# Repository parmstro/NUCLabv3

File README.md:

# NUCLabv3
Drawings, parts lists and instructions on building the latest version of NUC Lab.
Case Drawings use NewPowerBoardwPositioningHoles.fzz for power distribution board.

This is NUCLab3_Chassis1 (See the [Wiki](https://github.com/parmstro/NUCLabv3/wiki))

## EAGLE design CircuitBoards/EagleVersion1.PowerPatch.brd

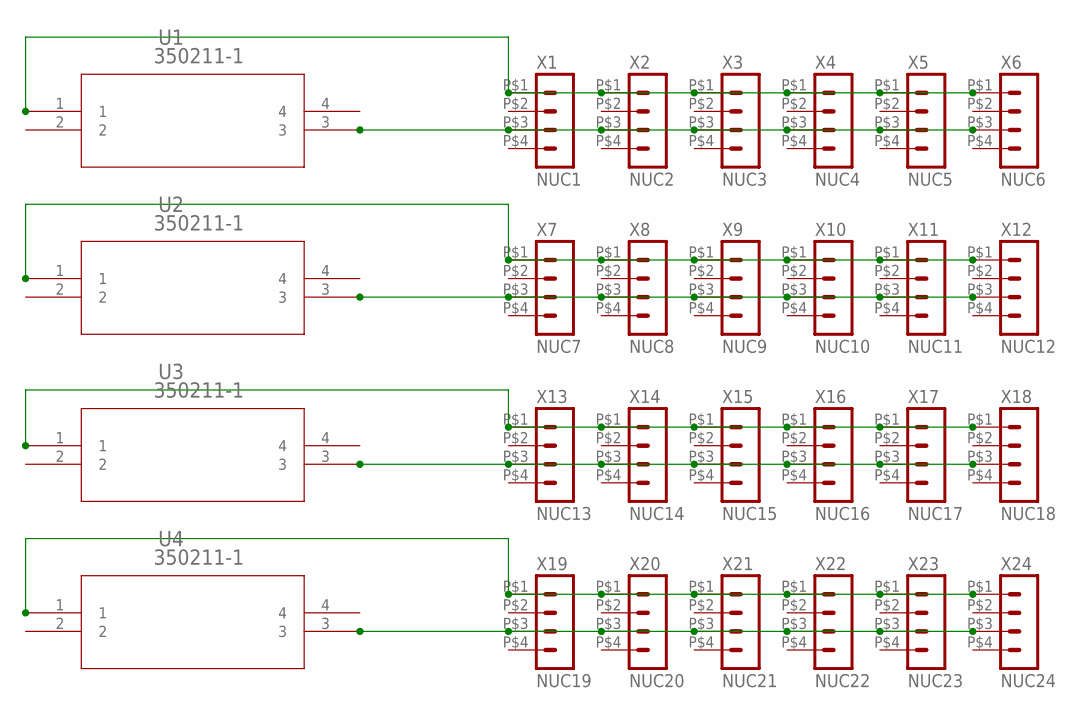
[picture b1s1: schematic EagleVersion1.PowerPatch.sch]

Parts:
U1, U2, U3, U4: 350211-1
X1: NUC1; 43045-0412
X2: NUC2; 43045-0412
X3: NUC3; 43045-0412
X4: NUC4; 43045-0412
X5: NUC5; 43045-0412
X6: NUC6; 43045-0412
X7: NUC7; 43045-0412
X8: NUC8; 43045-0412
X9: NUC9; 43045-0412
X10: NUC10; 43045-0412
X11: NUC11; 43045-0412
X12: NUC12; 43045-0412
X13: NUC13; 43045-0412
X14: NUC14; 43045-0412
X15: NUC15; 43045-0412
X16: NUC16; 43045-0412
X17: NUC17; 43045-0412
X18: NUC18; 43045-0412
X19: NUC19; 43045-0412
X20: NUC20; 43045-0412
X21: NUC21; 43045-0412
X22: NUC22; 43045-0412
X23: NUC23; 43045-0412
X24: NUC24; 43045-0412

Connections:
unnamed: U1.1, X1.P$1 (1), X2.P$1 (1), X3.P$1 (1), X4.P$1 (1), X5.P$1 (1), X6.P$1 (1)
unnamed: U1.3, X1.P$3 (3), X2.P$3 (3), X3.P$3 (3), X4.P$3 (3), X5.P$3 (3), X6.P$3 (3)
unnamed: U2.1, X7.P$1 (1), X8.P$1 (1), X9.P$1 (1), X10.P$1 (1), X11.P$1 (1), X12.P$1 (1)
unnamed: U2.3, X7.P$3 (3), X8.P$3 (3), X9.P$3 (3), X10.P$3 (3), X11.P$3 (3), X12.P$3 (3)
unnamed: U3.1, X13.P$1 (1), X14.P$1 (1), X15.P$1 (1), X16.P$1 (1), X17.P$1 (1), X18.P$1 (1)
unnamed: U3.3, X13.P$3 (3), X14.P$3 (3), X15.P$3 (3), X16.P$3 (3), X17.P$3 (3), X18.P$3 (3)
unnamed: U4.1, X19.P$1 (1), X20.P$1 (1), X21.P$1 (1), X22.P$1 (1), X23.P$1 (1), X24.P$1 (1)
unnamed: U4.3, X19.P$3 (3), X20.P$3 (3), X21.P$3 (3), X22.P$3 (3), X23.P$3 (3), X24.P$3 (3)

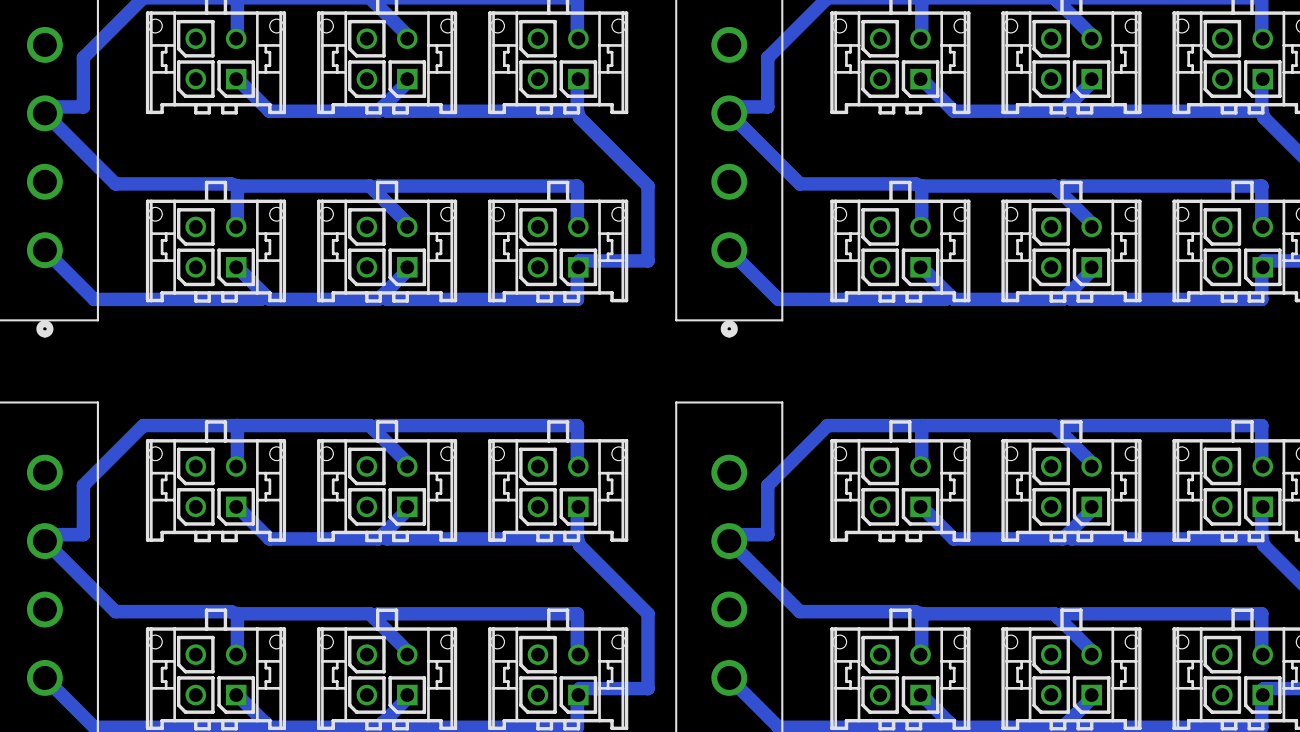
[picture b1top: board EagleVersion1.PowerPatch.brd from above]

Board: 2 copper layers, 28 parts (0 on the bottom side), 8 nets.

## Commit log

2022-03-10 Initial Drawing commit
2022-03-10 added circuits
2022-03-10 Update README.md
    pdb note
2022-11-22 NUCLab3_Chassis1.jpg added
    Picture of NUCLab3 powered up and running
2023-01-28 Separate Top Bottom, update text
2023-01-28 update comments
2023-01-28 increase offset on PS cutout to allow for switch raised edge
2023-01-29 Wiki link added
2023-01-29 closing bracket
2023-01-29 Add build images
2023-01-29 Case
2023-01-29 rotation and cropping

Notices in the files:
parts and their libraries:
COPYRIGHT: Copyright C 2015 Accelerated Designs. All rights reserved
